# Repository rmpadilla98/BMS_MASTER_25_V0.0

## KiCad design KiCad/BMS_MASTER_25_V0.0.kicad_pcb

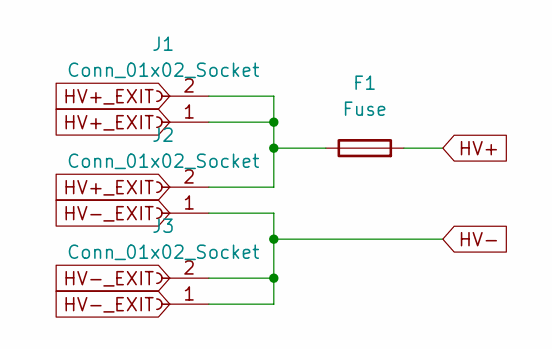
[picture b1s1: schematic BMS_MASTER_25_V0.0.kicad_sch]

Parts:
F1: Fuse; Fuseholder_Clip-5x20mm_Eaton_1A5601-01_Inline_P20.80x6.76mm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
J1, J2, J3: Conn_01x02_Socket; Molex_Micro-Fit_3.0_43650-0215_1x02_P3.00mm_Vertical

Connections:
HV+: F1.2
HV-: J2.1, J3.1, J3.2
unnamed: F1.1, J1.1, J1.2, J2.2

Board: 2 copper layers, 4 parts (0 on the bottom side), 2 nets, no tracks yet.

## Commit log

2025-12-29 Inicializa proyecto BMS_MASTER_25_V0.0 con estructura limpia
